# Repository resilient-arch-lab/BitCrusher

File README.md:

# BitCrusher: An Affordable, Open Source, Electromagnetic Fault Injection Platform
_NOTE: This repository is still under construction, and may be difficult to navigate in its current state_

Security researchers need attainable, effective tooling to secure computing infrastructure against physical attacks. Tools for hardware security research have been
getting cheaper and more effective over recent years, but EMFI tooling has been left behind. The cost of commercial EMFI tooling is typically on the order of tens to hundreds of thousands of dollars, and the highly-coupled proprietary equipment offers little insight to researchers developing or characterizing EMFI techniques. BitCrusher is being developed with the goal of addressing several challenges in this space:

- Supporting the continued improvement of open EMFI platform design techniques by contributing to the thread of research on the design of EMFI equipment
- Supporting the improvement of practical EMFI techniques and countermeasures through attainable and open domain specific instrumentation
- Lowering the high barrier to entry of replicating and expanding upon existing EMFI research by providing high performance equipment that is both affordable and easy to integrate with common existing hardware security instrumentation frameworks (e.g. ChipWhisperer)

## State of BitCrusher
BitCrusher was started as an undergraduate senior project in September 2025. Beginning April 2026, development efforts have been focused on working out design flaws and thoroughly verifying device performance.

See `/design.md` for status of ongoing design work.

## Licensing
Following the licensing guidelines of [OSHWA](https://oshwa.org/), the components of BitCrusher fall under a combination of OSI-approved licenses. The following licenses were selected with the goals of maximizing this work's benefit to the open hardware and open security research communities and ensuring potential commercial utilization of this work similarly benefits those communities.  

**Firmware and Software:** BitCrusher firmware and software fall under the [GNU Affero General Public License v3.0](https://www.gnu.org/licenses/agpl-3.0.html) (AGPL-3.0). This includes the BitCrusher device firmware (`/firmware`) and the host-side python interface (`/interface`).  

**Hardware design:** The design materials of BitCrusher (including but not limited to materials in `/design`, excluding those covered under the firmware / software licensing scheme) are licensed under the [CERN Open Hardware Licence Version 2 – Strongly Reciprocal](https://gitlab.com/ohwr/project/cernohl/-/wikis/uploads/819d71bea3458f71fba6cf4fb0f2de6b/cern_ohl_s_v2.txt) (CERN-OHL-S-2.0). 

**Documentation:** Current BitCrusher documentation, including but not limited to user guides / instructions, written documentation of the design, and written engineering work / documentation is under the [Creative Commons Attribution-ShareAlike 4.0 International](https://creativecommons.org/licenses/by-sa/4.0/) license (CC BY-SA 4.0). In cases where documentation is accompanied by code, such as simulations and calculations in `/design-resources`, the code falls under the AGPL-3.0 license while the written work falls under the CC BY-SA 4.0 license. 

While there is currently no sound structure for project governance, the policy for potential future contributions to the project's documentation is that the contributions should be CC BY-SA 4.0 licensed under the title "BitCrusher" and attributed to the respective contributor(s).  

**Branding:** Since this work was named after the [digital audio effect](https://en.wikipedia.org/wiki/Bitcrusher), as well as the fact that this project is a non-commercial endeavor, no restrictions apply to the use of the name BitCrusher.

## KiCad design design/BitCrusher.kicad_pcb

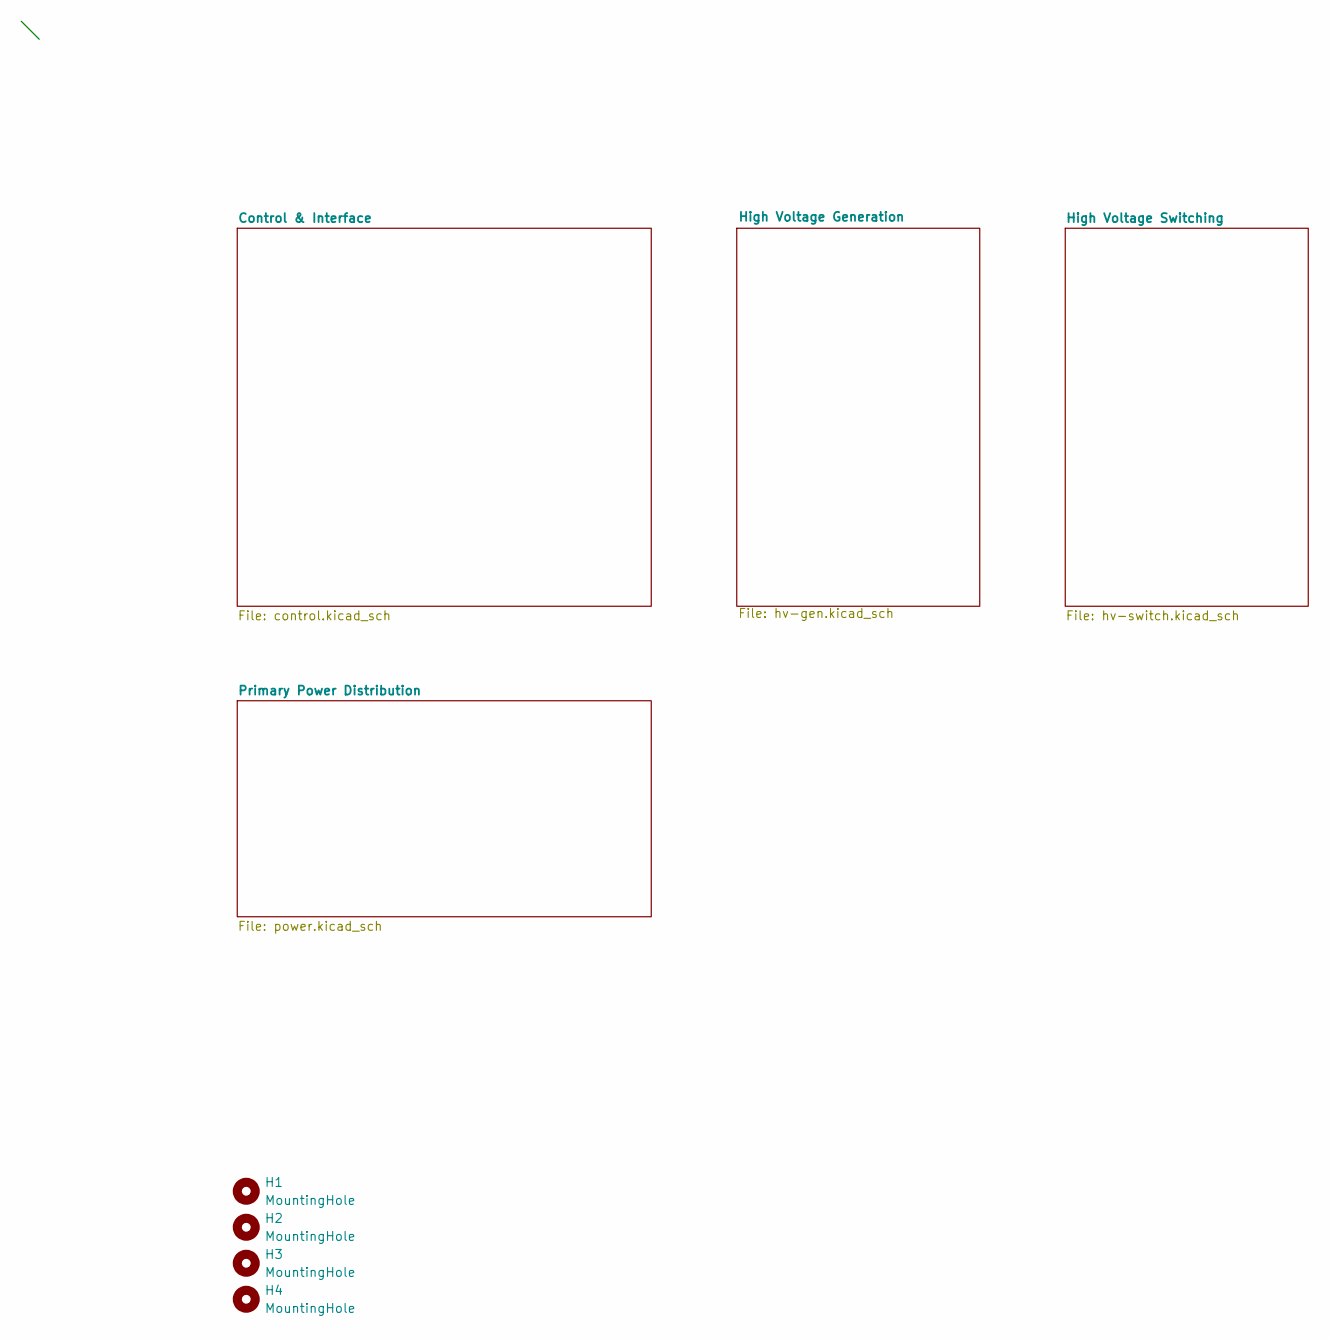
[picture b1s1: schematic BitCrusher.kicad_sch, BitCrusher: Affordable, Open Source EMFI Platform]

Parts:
H1, H2, H3, H4: MountingHole; MountingHole_3.2mm_M3

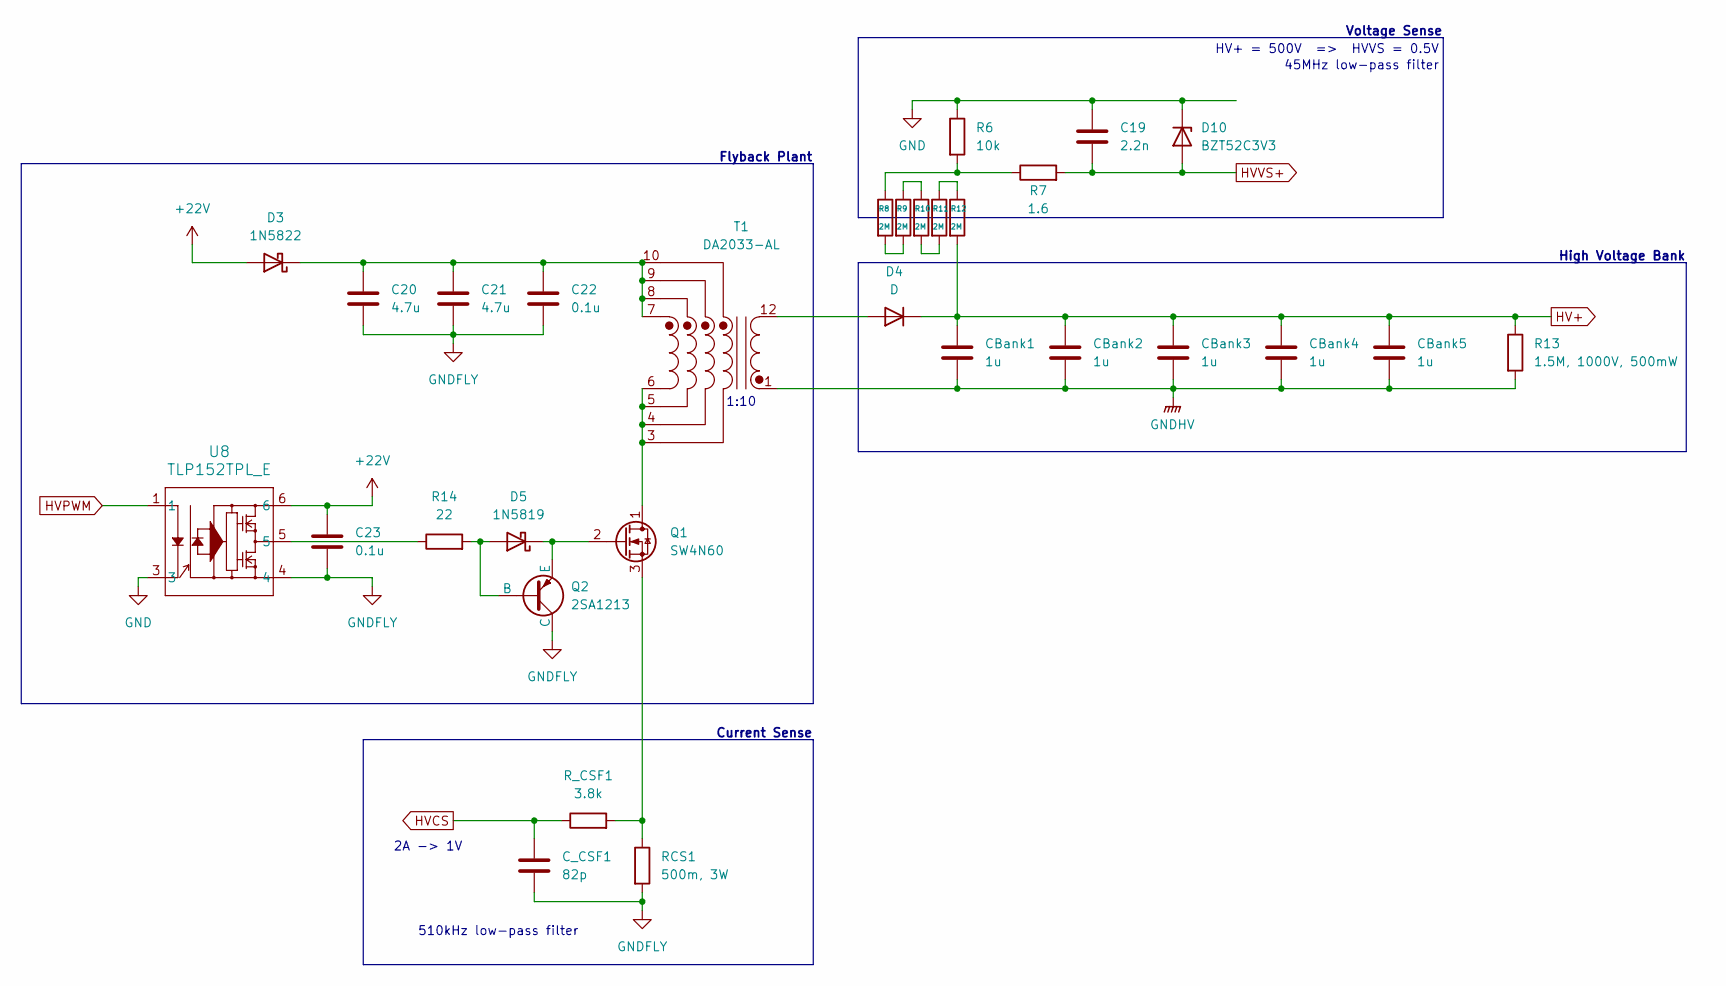
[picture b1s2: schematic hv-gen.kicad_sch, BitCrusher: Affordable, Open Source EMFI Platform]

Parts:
C19: 2.2n; C_0603_1608Metric
C20, C21: 4.7u; C_0402_1005Metric
C22: 0.1u; C_0402_1005Metric
C23: 0.1u; C_1206_3216Metric
CBank1, CBank2, CBank3, CBank4, CBank5: 1u; C_2220_5750Metric; JLCPCB# C784102
C_CSF1: 82p; C_0402_1005Metric
D3: 1N5822; D_DO-201AD_P12.70mm_Horizontal
D4: D; D_SMA
D5: 1N5819; D_SOD-323
D10: BZT52C3V3; D_SOD-123
Q1: SW4N60
Q2: 2SA1213; SOT-89-3
R6: 10k; R_0603_1608Metric
R7: 1.6; R_0603_1608Metric
R8, R9, R10, R11, R12: 2M; R_0805_2012Metric
R13: 1.5M, 1000V, 500mW; R_Axial_DIN0414_L11.9mm_D4.5mm_P15.24mm_Horizontal; JLCPCB# C30187384
R14: 22; R_0805_2012Metric
RCS1: 500m, 3W; R_2512_6332Metric
R_CSF1: 3.8k; R_0402_1005Metric
T1: DA2033-AL; SOP254P2413X978-12N
U8: TLP152TPL_E; TLP152_4P55X3P7_TOS

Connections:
+22V: C23.1, D3.2 (A), U8.6; also elsewhere on the board
GND: C19.1, D10.1 (K), R6.1, U8.3; also elsewhere on the board
GNDFLY: C20.2, C21.2, C22.2, C23.2, C_CSF1.2, Q2.C, RCS1.2, U8.4; also elsewhere on the board
HV+: CBank1.1, CBank2.1, CBank3.1, CBank4.1, CBank5.1, D4.1 (K), R12.2, R13.1; also elsewhere on the board
HVCS: C_CSF1.1, R_CSF1.1; also elsewhere on the board
HVPWM: U8.1; also elsewhere on the board
HVVS+: C19.2, D10.2 (A), R7.2; also elsewhere on the board
unnamed: C20.1, C21.1, C22.1, D3.1 (K), T1.7, T1.8, T1.9, T1.10
unnamed: D4.2 (A), T1.12
unnamed: D5.2 (A), Q2.B, R14.2
unnamed: D5.1 (K), Q1.2 (G), Q2.E
unnamed: Q1.1 (D), T1.3, T1.4, T1.5, T1.6
unnamed: Q1.3 (S), RCS1.1, R_CSF1.2
unnamed: R6.2, R7.1, R8.1
unnamed: R8.2, R9.2
unnamed: R9.1, R10.1
unnamed: R10.2, R11.2
unnamed: R11.1, R12.1
unnamed: R14.1, U8.5
PulseCS-: CBank1.2, CBank2.2, CBank3.2, CBank4.2, CBank5.2, R13.2, T1.1; also elsewhere on the board

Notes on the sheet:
High Voltage Bank
510kHz low-pass filter
Flyback Plant
2A -> 1V
1:10
Current Sense
HV+ = 500V => HVVS = 0.5V
Voltage Sense
45MHz low-pass filter

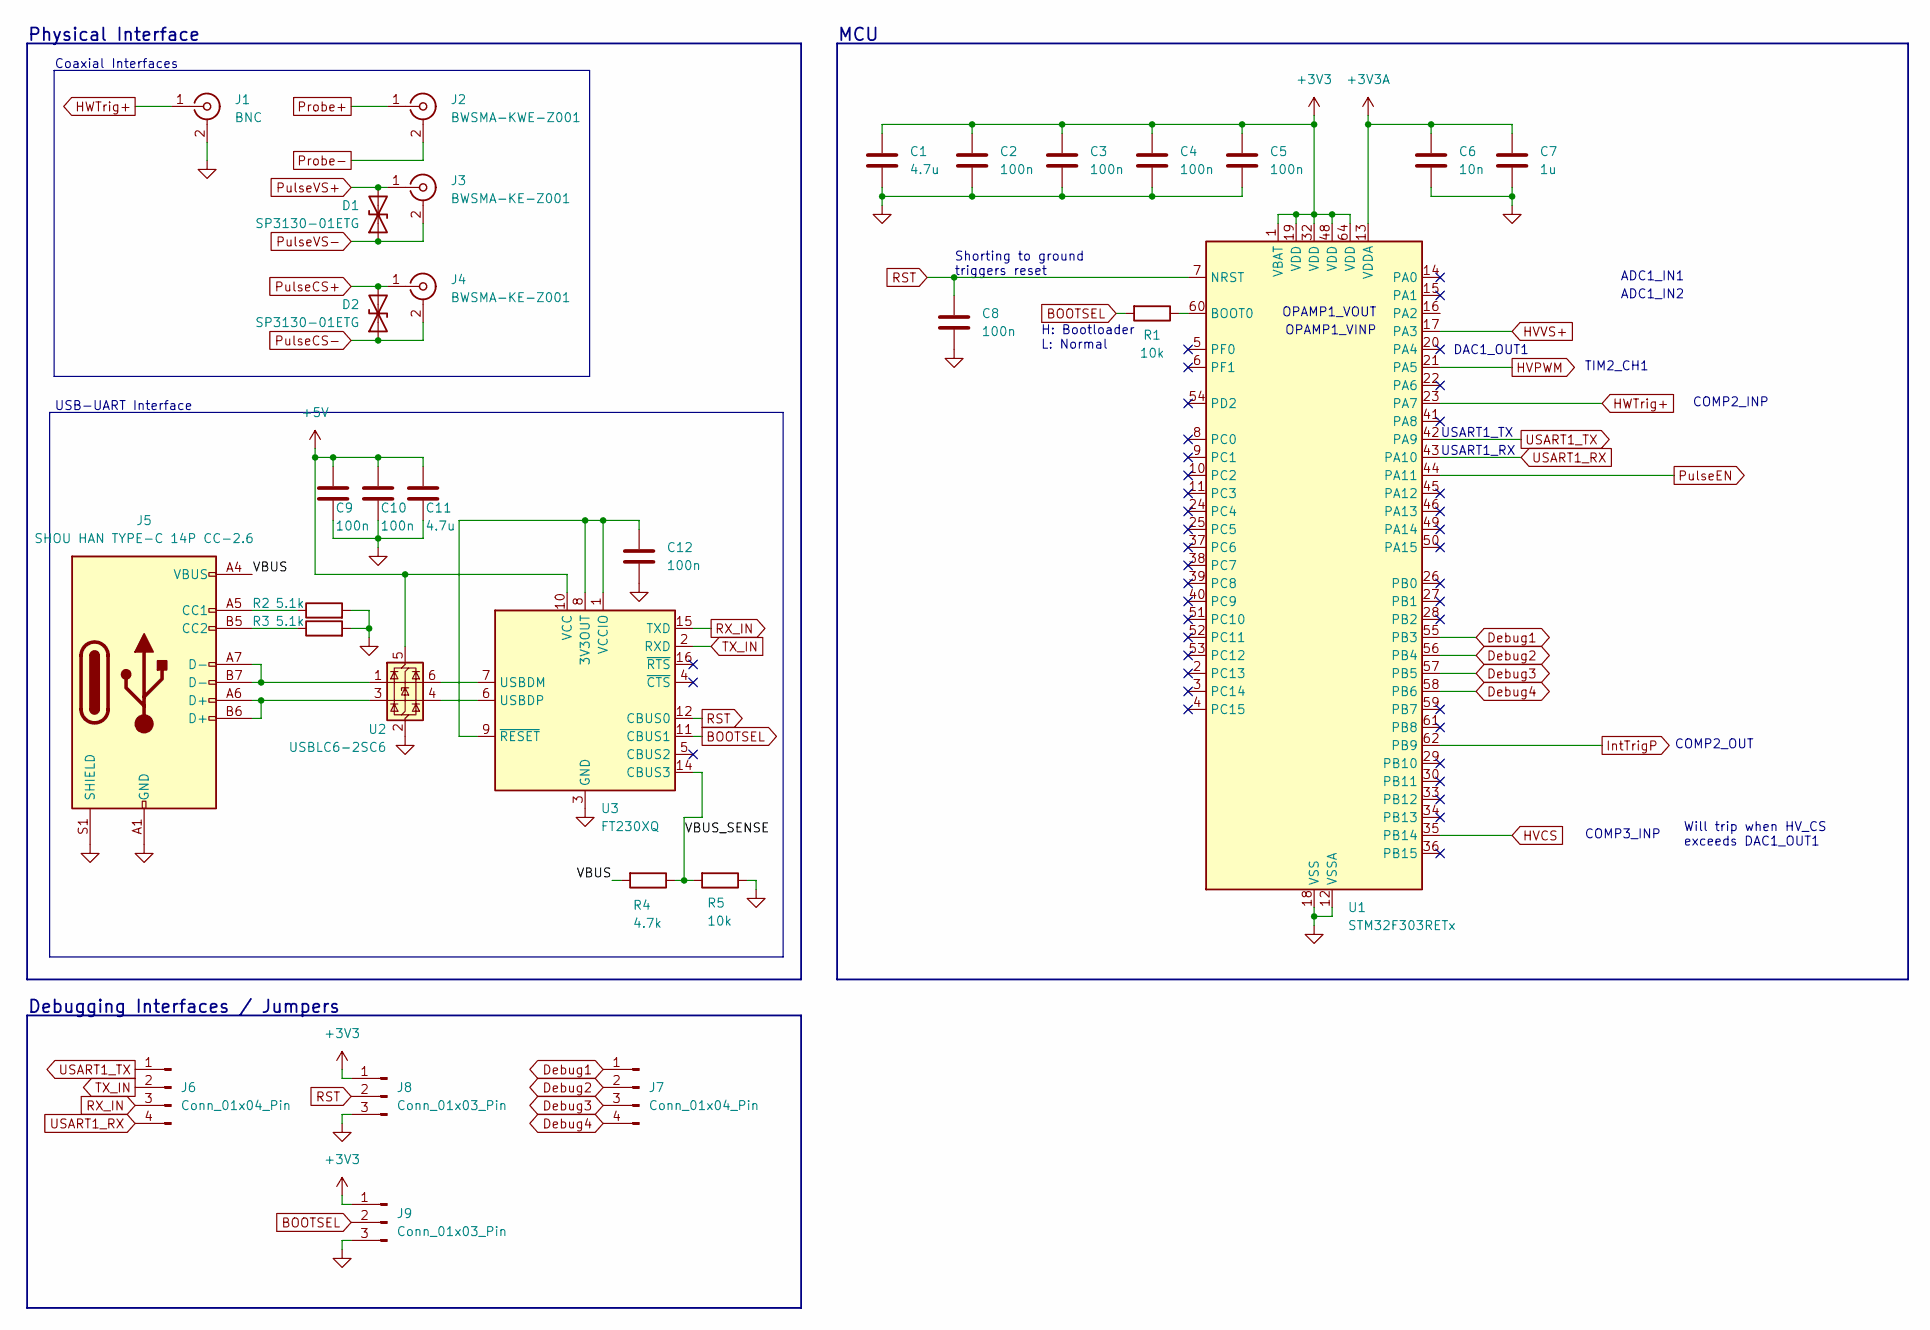
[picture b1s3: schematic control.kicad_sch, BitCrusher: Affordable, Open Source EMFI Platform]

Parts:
C1, C11: 4.7u; C_0402_1005Metric
C2, C3, C4, C5, C8, C9, C10, C12: 100n; C_0402_1005Metric
C6: 10n; C_0402_1005Metric
C7: 1u; C_0402_1005Metric
D1, D2: SP3130-01ETG; D_SOD-882
J1: BNC; KHBNC503511
J2: BWSMA-KWE-Z001; SMA_BAT_Wireless_BWSMA-KWE-Z001
J3, J4: BWSMA-KE-Z001; SMA_BAT_Wireless_BWSMA-KE-Z001
J5: SHOU HAN TYPE-C 14P CC-2.6; TYPE-C-TH_TYPE-C-14P-CC-2.6
J6, J7: Conn_01x04_Pin; PinHeader_1x04_P2.54mm_Vertical
J8, J9: Conn_01x03_Pin; PinHeader_1x03_P2.54mm_Vertical
R1, R5: 10k; R_0402_1005Metric
R2, R3: 5.1k; R_0603_1608Metric
R4: 4.7k; R_0402_1005Metric
U1: STM32F303RETx; LQFP-64_10x10mm_P0.5mm
U2: USBLC6-2SC6; SOT-23-6
U3: FT230XQ; QFN-16-1EP_4x4mm_P0.65mm_EP2.1x2.1mm

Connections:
+3V3: C1.1, C2.1, C3.1, C4.1, C5.1, C6.1, C7.1, J8.1, J9.1, U1.1 (VBAT), U1.13 (VDDA), U1.19 (VDD), U1.32 (VDD), U1.48 (VDD), U1.64 (VDD); also elsewhere on the board
+5V: C9.1, C10.1, C11.1, U2.5 (VBUS), U3.10 (VCC); also elsewhere on the board
/Control & Interface/VBUS: J5.A4 (VBUS), J5.A9 (VBUS), J5.B4 (VBUS), J5.B9 (VBUS), R4.2
/Control & Interface/VBUS_SENSE: R4.1, R5.2, U3.14 (CBUS3)
BOOTSEL: J9.2, R1.2, U3.11 (CBUS1)
Debug1: J7.1, U1.55 (PB3)
Debug2: J7.2, U1.56 (PB4)
Debug3: J7.3, U1.57 (PB5)
Debug4: J7.4, U1.58 (PB6)
GND: C1.2, C2.2, C3.2, C4.2, C5.2, C6.2, C7.2, C8.2, C9.2, C10.2, C11.2, C12.2, J1.2 (Ext), J5.A1 (GND), J5.A12 (GND), J5.B1 (GND), J5.B12 (GND), J5.S1 (SHIELD), J8.3, J9.3, R2.2, R3.2, R5.1, U1.12 (VSSA), U1.18 (VSS), U1.31 (VSS), U1.47 (VSS), U1.63 (VSS), U2.2 (GND), U3.3 (GND), U3.13 (GND), U3.17 (GND); also elsewhere on the board
HVCS: U1.35 (PB14); also elsewhere on the board
HVPWM: U1.21 (PA5); also elsewhere on the board
HVVS+: U1.17 (PA3); also elsewhere on the board
HWTrig+: J1.1 (In), U1.23 (PA7)
IntTrigP: U1.62 (PB9); also elsewhere on the board
unnamed: J5.A5 (CC1), R2.1
unnamed: J5.B5 (CC2), R3.1
unnamed: J5.A6 (D+), J5.B6 (D+), U2.3 (I/O2)
unnamed: J5.A7 (D-), J5.B7 (D-), U2.1 (I/O1)
unnamed: R1.1, U1.60 (BOOT0)
unnamed: C12.1, U3.1 (VCCIO), U3.8 (3V3OUT), U3.9 (~RESET)
unnamed: U2.6 (I/O1), U3.7 (USBDM)
unnamed: U2.4 (I/O2), U3.6 (USBDP)
Probe+: J2.1 (In); also elsewhere on the board
Probe-: J2.2 (Ext); also elsewhere on the board
PulseCS+: D2.2 (A2), J4.1 (In); also elsewhere on the board
PulseCS-: D1.1 (A1), D2.1 (A1), J3.2 (Ext), J4.2 (Ext); also elsewhere on the board
PulseEN: U1.44 (PA11); also elsewhere on the board
PulseVS+: D1.2 (A2), J3.1 (In); also elsewhere on the board
RST: C8.1, J8.2, U1.7 (NRST), U3.12 (CBUS0)
RX_IN: J6.3, U3.15 (TXD)
TX_IN: J6.2, U3.2 (RXD)
USART1_RX: J6.4, U1.43 (PA10)
USART1_TX: J6.1, U1.42 (PA9)

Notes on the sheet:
OPAMP1_VINP
ADC1_IN2
COMP2_INP
USART1_TX
H: Bootloader L: Normal
TIM2_CH1
ADC1_IN1
MCU
Debugging Interfaces / Jumpers
DAC1_OUT1
COMP2_OUT
Shorting to ground triggers reset
USB-UART Interface
USART1_RX
OPAMP1_VOUT
Coaxial Interfaces
Will trip when HV_CS exceeds DAC1_OUT1
COMP3_INP
Physical Interface

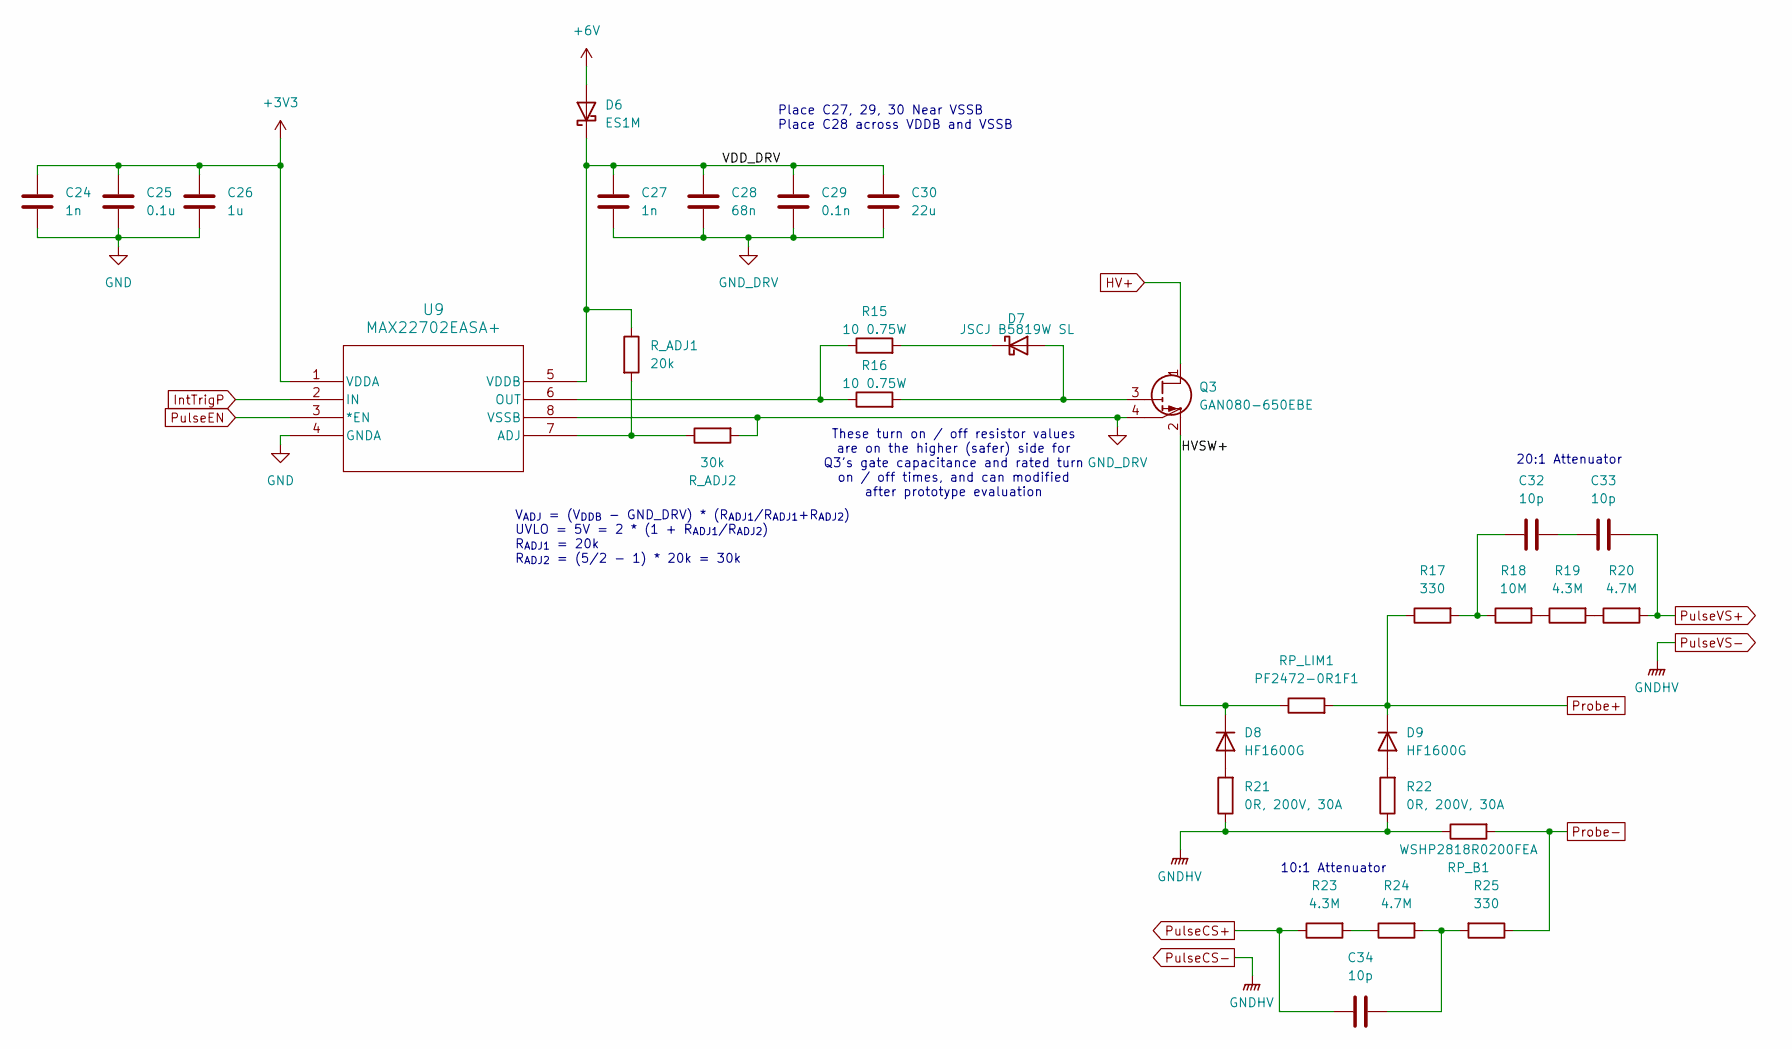
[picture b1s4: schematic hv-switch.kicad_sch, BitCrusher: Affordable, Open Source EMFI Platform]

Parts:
C24, C27: 1n; C_0402_1005Metric
C25: 0.1u; C_0402_1005Metric
C26: 1u; C_0402_1005Metric
C28: 68n; C_1206_3216Metric
C29: 0.1n; C_0402_1005Metric
C30: 22u; C_0603_1608Metric; JLCPCB# C60077
C32, C33, C34: 10p; C_0402_1005Metric
D6: ES1M; D_SMA
D7: JSCJ B5819W SL; D_SOD-123
D8, D9: HF1600G; D_DO-41_SOD81_P7.62mm_Horizontal
Q3: GAN080-650EBE; GAN080650EBEZ
R15, R16: 10 0.75W; R_1206_3216Metric
R17: 330; R_0603_1608Metric
R18: 10M; R_0603_1608Metric
R19, R23: 4.3M; R_0603_1608Metric
R20, R24: 4.7M; R_0603_1608Metric
R21, R22: 0R, 200V, 30A; R_2512_6332Metric
R25: 330; R_2512_6332Metric
RP_B1: WSHP2818R0200FEA
RP_LIM1: PF2472-0R1F1; TO-247-2_Horizontal_TabDown
R_ADJ1: 20k; R_0402_1005Metric
R_ADJ2: 30k; R_0402_1005Metric
U9: MAX22702EASA+; 21-0041-A_8L

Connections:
+3V3: C24.1, C25.1, C26.1, U9.1 (VDDA); also elsewhere on the board
+6V: D6.2 (A); also elsewhere on the board
/High Voltage Switching/HVSW+: D8.1 (K), Q3.2 (S), RP_LIM1.1
/High Voltage Switching/VDD_DRV: C27.1, C28.1, C29.1, C30.1, D6.1 (K), R_ADJ1.1, U9.5 (VDDB)
GND: C24.2, C25.2, C26.2, U9.4 (GNDA); also elsewhere on the board
GND_DRV: C27.2, C28.2, C29.2, C30.2, Q3.4 (SS), R_ADJ2.2, U9.8 (VSSB)
HV+: Q3.1 (D); also elsewhere on the board
IntTrigP: U9.2 (IN); also elsewhere on the board
unnamed: C32.1, C33.2
unnamed: C32.2, R17.2, R18.1
unnamed: C34.2, R24.2, R25.2
unnamed: D7.2 (A), Q3.3 (G), R16.2
unnamed: D7.1 (K), R15.2
unnamed: D8.2 (A), R21.2
unnamed: D9.2 (A), R22.2
unnamed: R18.2, R19.1
unnamed: R19.2, R20.1
unnamed: R23.2, R24.1
unnamed: R_ADJ1.2, R_ADJ2.1, U9.7 (ADJ)
unnamed: R15.1, R16.1, U9.6 (OUT)
Probe+: D9.1 (K), R17.1, RP_LIM1.2; also elsewhere on the board
Probe-: R25.1, RP_B1.2; also elsewhere on the board
PulseCS+: C34.1, R23.1; also elsewhere on the board
PulseCS-: R21.1, R22.1, RP_B1.1; also elsewhere on the board
PulseEN: U9.3 (*EN); also elsewhere on the board
PulseVS+: C33.1, R20.2; also elsewhere on the board

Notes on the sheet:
These turn on / off resistor values are on the higher (safer) side for Q3's gate capacitance and rated turn on / off times, and can modified after prototype evaluation
10:1 Attenuator
V_{ADJ} = (V_{DDB} - GND_DRV) * (R_{ADJ1}/R_{ADJ1}+R_{ADJ2}) UVLO = 5V = 2 * (1 + R_{ADJ1}/R_{ADJ2}) R_{ADJ1} = 20k R_{ADJ2} = (5/2 - 1) * 20k = 30k
20:1 Attenuator
Place C27, 29, 30 Near VSSB Place C28 across VDDB and VSSB

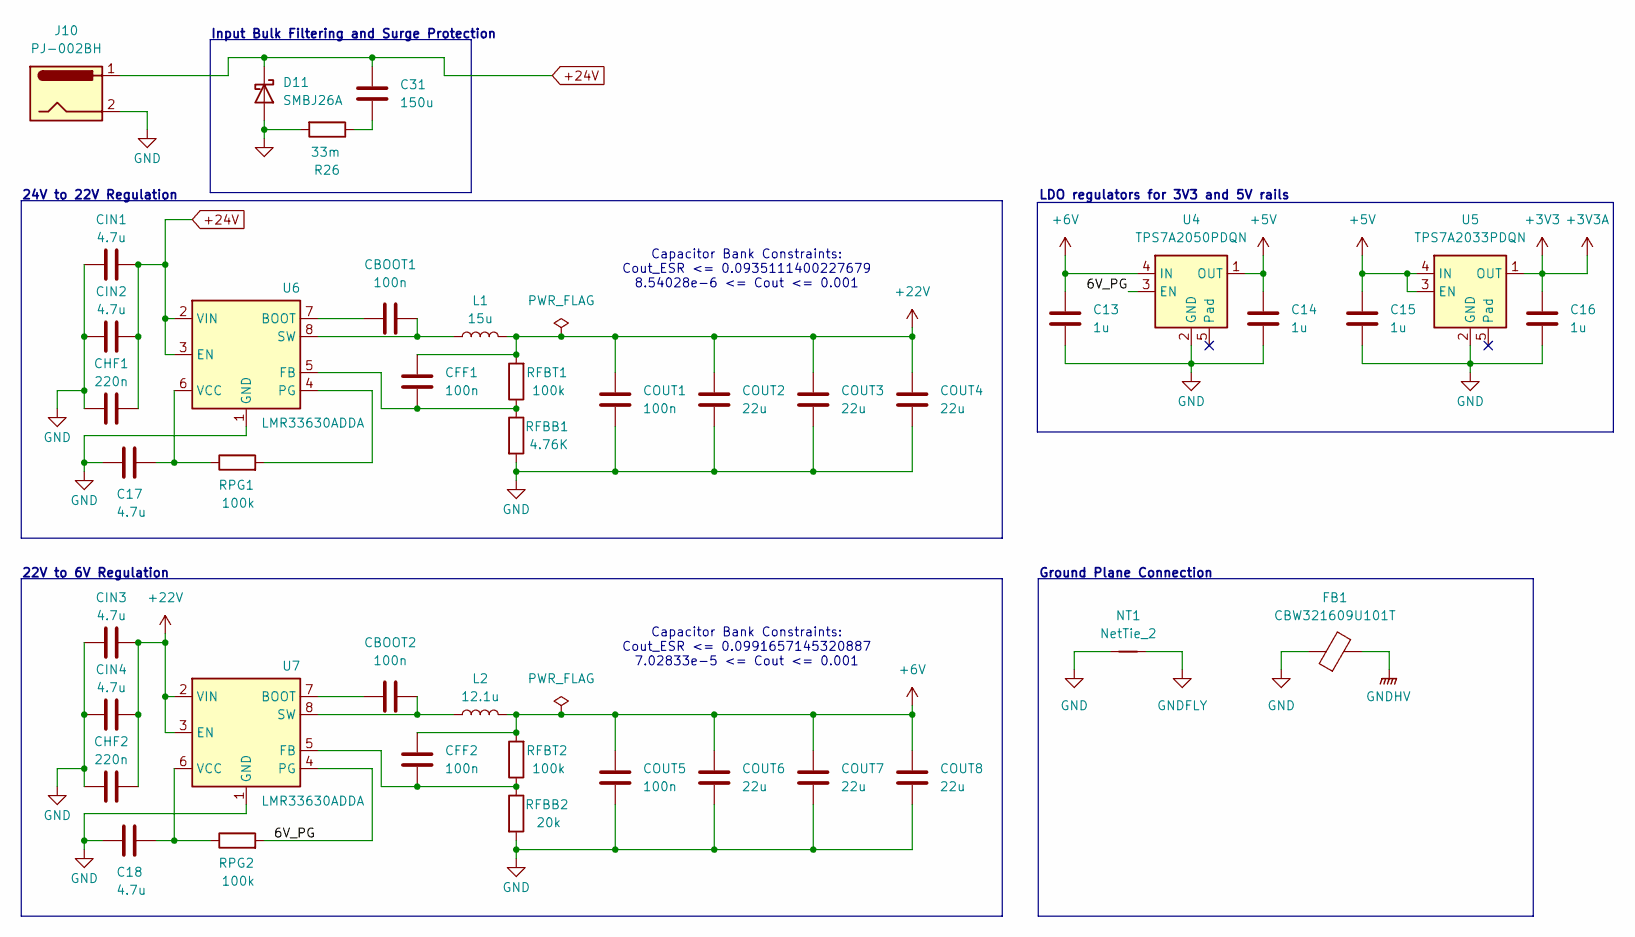
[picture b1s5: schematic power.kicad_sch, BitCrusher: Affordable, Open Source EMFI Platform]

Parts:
C13, C14, C15, C16: 1u; C_0402_1005Metric
C17, C18: 4.7u; C_1206_3216Metric
C31: 150u; C_Radial_D10.0mm_H20.0mm_P5.00mm
CBOOT1, CBOOT2: 100n; C_0402_1005Metric
CFF1, CFF2: 100n; C_0402_1005Metric
CHF1, CHF2: 220n; C_0805_2012Metric
CIN1, CIN2, CIN3, CIN4: 4.7u; C_1206_3216Metric
COUT1, COUT5: 100n; C_0402_1005Metric
COUT2, COUT3, COUT4, COUT6, COUT7, COUT8: 22u; C_1210_3225Metric
D11: SMBJ26A; D_SMB
FB1: CBW321609U101T; L_1206_3216Metric
J10: PJ-002BH; PJ-002B_CUI
L1: 15u; L_TechFuse_SL0630
L2: 12.1u; L_TechFuse_SL0630
NT1: NetTie_2; NetTie-2_SMD_Pad2.0mm
R26: 33m; R_0603_1608Metric
RFBB1: 4.76K; R_0603_1608Metric
RFBB2: 20k; R_0603_1608Metric
RFBT1, RFBT2: 100k; R_0603_1608Metric
RPG1, RPG2: 100k; R_0603_1608Metric
U4: TPS7A2050PDQN; Texas_X2SON-4_1x1mm_P0.65mm
U5: TPS7A2033PDQN; Texas_X2SON-4_1x1mm_P0.65mm
U6, U7: LMR33630ADDA; Texas_HSOP-8-1EP_3.9x4.9mm_P1.27mm_ThermalVias

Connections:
+3V3: C16.1, U5.1 (OUT); also elsewhere on the board
+5V: C14.1, C15.1, U4.1 (OUT), U5.3 (EN), U5.4 (IN); also elsewhere on the board
+6V: C13.1, CFF2.2, COUT5.2, COUT6.2, COUT7.2, COUT8.2, L2.2, RFBT2.2, U4.4 (IN); also elsewhere on the board
+22V: CFF1.2, CHF2.1, CIN3.1, CIN4.1, COUT1.2, COUT2.2, COUT3.2, COUT4.2, L1.2, RFBT1.2, U7.2 (VIN), U7.3 (EN); also elsewhere on the board
+24V: C31.1, CHF1.1, CIN1.1, CIN2.1, D11.1 (K), J10.1, U6.2 (VIN), U6.3 (EN)
/Primary Power Distribution/6V_PG: RPG2.2, U4.3 (EN), U7.4 (PG)
GND: C13.2, C14.2, C15.2, C16.2, C17.2, C18.2, CHF1.2, CHF2.2, CIN1.2, CIN2.2, CIN3.2, CIN4.2, COUT1.1, COUT2.1, COUT3.1, COUT4.1, COUT5.1, COUT6.1, COUT7.1, COUT8.1, D11.2 (A), FB1.1, J10.2, NT1.1, R26.2, RFBB1.2, RFBB2.2, U4.2 (GND), U5.2 (GND), U6.1 (GND), U6.9 (GND), U7.1 (GND), U7.9 (GND); also elsewhere on the board
GNDFLY: NT1.2; also elsewhere on the board
unnamed: C31.2, R26.1
unnamed: CBOOT1.1, U6.7 (BOOT)
unnamed: CFF1.1, RFBB1.1, RFBT1.1, U6.5 (FB)
unnamed: RPG1.2, U6.4 (PG)
unnamed: CBOOT1.2, L1.1, U6.8 (SW)
unnamed: C17.1, RPG1.1, U6.6 (VCC)
unnamed: CBOOT2.1, U7.7 (BOOT)
unnamed: CFF2.1, RFBB2.1, RFBT2.1, U7.5 (FB)
unnamed: CBOOT2.2, L2.1, U7.8 (SW)
unnamed: C18.1, RPG2.1, U7.6 (VCC)
PulseCS-: FB1.2; also elsewhere on the board

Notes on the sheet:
24V to 22V Regulation
Capacitor Bank Constraints: Cout_ESR <= 0.0991657145320887 7.02833e-5 <= Cout <= 0.001
LDO regulators for 3V3 and 5V rails
Capacitor Bank Constraints: Cout_ESR <= 0.0935111400227679 8.54028e-6 <= Cout <= 0.001
Ground Plane Connection
Input Bulk Filtering and Surge Protection
22V to 6V Regulation

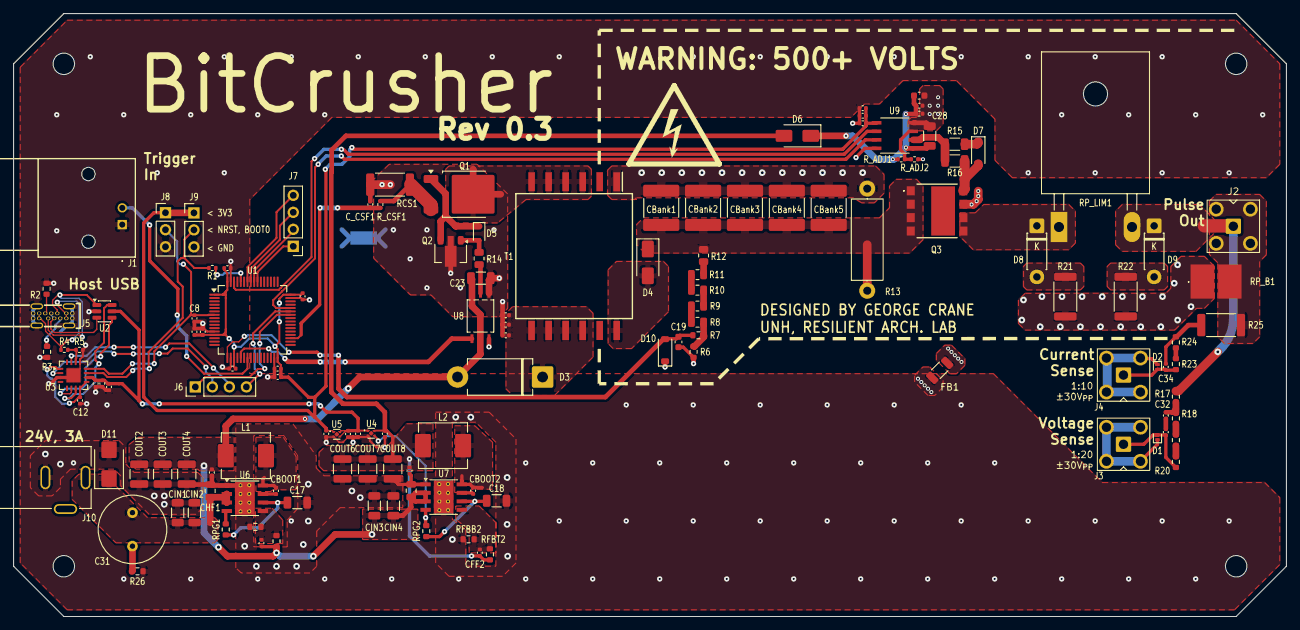
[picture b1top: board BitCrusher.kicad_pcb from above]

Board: 2 copper layers, 190.0 x 90.0 mm, 138 parts (1 on the bottom side), 77 nets.

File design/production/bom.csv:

Designator,Footprint,Quantity,Value,LCSC Part #
C_CSF1,402,1,82p,C107011
"C1, C11, C20, C21",402,4,4.7u,C2858031
"C10, C12, C2, C3, C4, C5, C8, C9, CBOOT1, CBOOT2, CFF1, CFF2, COUT1, COUT5",402,14,100n,C1525
"C13, C15, C26, C7",402,4,1u,C52923
"C14, C16",402,2,5u,C29266
"C17, C18, CIN1, CIN2, CIN3, CIN4",1206,6,4.7u,C29823
C19,603,1,2.2n,C1604
"C22, C25",402,2,0.1u,C1525
C23,1206,1,0.1u,C24497
"C24, C27",402,2,1n,C1523
C28,1206,1,68n,C711038
C29,402,1,0.1n,C343055
C30,603,1,22u,C60077
"C32, C33, C34",402,3,10p,C32949
C6,402,1,10n,C1524
"CBANK1, CBANK2, CBANK3, CBANK4, CBANK5",2220,5,1u,C784102
"CHF1, CHF2",805,2,220n,C5378
"COUT2, COUT3, COUT4, COUT6, COUT7, COUT8",1210,6,22u,C21397
"D1, D2",D_SOD-882,2,SP3031-01ETG,C207283
D10,D_SOD-123,1,BZT52C3V3,C19077396
"D3, D6",D_DO-201AD_P12.70mm_Horizontal,2,1N5822,C2476
D4,D_SMA,1,D,C64958
D5,D_SOD-323,1,1N5819,C191023
D7,D_SOD-123,1,D_Schottky,C8598
"D8, D9",D_DO-41_SOD81_P7.62mm_Horizontal,2,HF1600G,C411154
FB1,1206,1,CBW321609U101T,C91466
J1,KHBNC503511,1,BNC,C2837587
J10,PJ-002B_CUI,1,PJ-002BH,C22359705
J2,SMA_BAT_Wireless_BWSMA-KWE-Z001,1,BWSMA-KWE-Z001,C496551
"J3, J4",SMA_BAT_Wireless_BWSMA-KE-Z001,2,BWSMA-KE-Z001,C496549
J5,TYPE-C-TH_TYPE-C-14P-CC-2.6,1,SHOU HAN TYPE-C 14P CC-2.6,C5187475
"J6, J7",PinHeader_1x04_P2.54mm_Vertical,2,Conn_01x04_Pin,
"J8, J9",PinHeader_1x03_P2.54mm_Vertical,2,Conn_01x03_Pin,
L1,L_TechFuse_SL0630,1,15u,C22463824
L2,L_TechFuse_SL0630,1,12.1u,C22463823
Q1,SW4N60,1,SW4N60,C381523
Q2,SOT-89-3,1,2SA1213,C20069144
Q3,GAN080650EBEZ,1,GAN080-650EBE,C20235155
R_ADJ1,402,1,20k,C25545
R_ADJ2,402,1,30k,C49652989
R_CSF1,402,1,3.8k,C51721
"R1, R5",402,2,10k,C25744
"R10, R11, R12, R8, R9",805,5,2M,C26112
R13,R_Axial_DIN0414_L11.9mm_D4.5mm_P15.24mm_Horizontal,1,"1.5M, 1000V, 500mW",C30187384
R14,805,1,22,C17561
"R15, R16",1206,2,10 0.75W,C873970
R17,603,1,330,C23138
R18,603,1,10M,C7250
"R19, R23",603,2,4.3M,C2930152
"R2, R3",603,2,5.1k,C23186
"R20, R24",603,2,4.7M,C23163
"R21, R22",2512,2,"0R, 200V, 30A",C2907567
R25,2512,1,330,C4134246
R26,603,1,0,C21189
R4,402,1,4.7k,C25900
R6,603,1,60k,C6460576
R7,603,1,1.6,C2930144
RCS1,2512,1,"500m, 3W",C2904268
RFBB1,603,1,4.76K,C23045
RFBB2,603,1,20k,C4184
"RFBT1, RFBT2, RPG1, RPG2",603,4,100k,C25803
RP_B1,WSHP2818R0200FEA,1,WSHP2818R0200FEA,C2090752
RP_LIM1,TO-247-2_Horizontal_TabDown,1,PF2472-0R1F1,C3387781
T1,SOP254P2413X978-12N,1,DA2033-AL,C5142798
U1,LQFP-64_10x10mm_P0.5mm,1,STM32F303RETx,C183214
U2,SOT-23-6,1,USBLC6-2SC6,C2827654
U3,QFN-16-1EP_4x4mm_P0.65mm_EP2.1x2.1mm,1,FT230XQ,C128629
U4,Texas_X2SON-4_1x1mm_P0.65mm,1,TPS7A2050PDQN,C2866499
U5,Texas_X2SON-4_1x1mm_P0.65mm,1,TPS7A2033PDQN,C2871641
"U6, U7",Texas_HSOP-8-1EP_3.9x4.9mm_P1.27mm_ThermalVias,2,LMR33630ADDA,C2866787
U8,TLP152_4P55X3P7_TOS,1,TLP152TPL_E,C150122
U9,21-0041-A_8L,1,MAX22702EASA+,C17268134

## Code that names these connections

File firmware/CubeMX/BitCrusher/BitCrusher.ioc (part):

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Mcu.Name=STM32F303R(D-E)Tx
Mcu.Package=LQFP64
Mcu.UserName=STM32F303RETx
PA0.GPIOParameters=GPIO_Label
PA0.GPIO_Label=HVSense+
PA0.Mode=IN1-Differential
PA0.Signal=ADC1_IN1
PA1.GPIOParameters=GPIO_Label
PA1.GPIO_Label=HVSense-
PA1.Mode=IN1-Differential
PA1.Signal=ADC1_IN2
PA10.Mode=Asynchronous
PA10.Signal=USART1_RX
PA11.GPIOParameters=GPIO_Label
PA11.GPIO_Label=PulseEN
PA11.Signal=GPIO_Output
PA2.Mode=PGA Not Connected
PA2.Signal=OPAMP1_VOUT
PA3.Mode=PGA Not Connected
PA3.Signal=OPAMP1_VINP
PA4.Signal=COMP_DAC11_group
PA5.GPIOParameters=GPIO_Label
PA5.GPIO_Label=HVPWM
PA5.Signal=S_TIM2_CH1_ETR
PA6.Signal=S_TIM3_CH1
PA7.GPIOParameters=GPIO_Label
PA7.GPIO_Label=HWTrig+
PA7.Mode=INP
PA7.Signal=COMP2_INP
PA9.Mode=Asynchronous
PA9.Signal=USART1_TX
PB14.GPIOParameters=GPIO_Label
PB14.GPIO_Label=HVCS
PB14.Mode=INP
PB14.Signal=COMP3_INP
PB9.GPIOParameters=GPIO_Label
PB9.GPIO_Label=IntTrig+
PB9.Mode=ExternalOutput
PB9.Signal=COMP2_OUT
PD2.Signal=S_TIM3_ETR
RCC.HSE_VALUE=8000000
RCC.SYSCLKFreq_VALUE=72000000
RCC.SYSCLKSourceVirtual=RCC_SYSCLKSOURCE_PLLCLK
board=custom

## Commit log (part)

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2025-11-08 added kicad project
2025-11-08 added .gitignore
2025-11-09 started microcontroller setup
2025-11-09 added cubemx project for microcontroller
2025-11-10 started primary power distribution design
2025-11-12 hv generation planning
2025-11-26 added CubeMX files, worked on microcontroller schematic
2025-11-28 figuring out triggering scheme
2025-12-01 started USB-C interface design
2025-12-05 Working on GaNFET driver circuit for HV switching
2025-12-07 Working on high voltage switching
2025-12-20 assembling final components for HV switching
2025-12-21 Continuing work on HV switching and primary power distribution
2025-12-26 Finished flyback voltage sense divider
2025-12-27 Working on probe voltage and current sense circuits
2025-12-28 outlining python interface
2025-12-30 Trying to figure out high side driver level shifting
2025-12-31 Fixed gate drive UVLO
2026-01-04 Added low pass filter to high voltage sensing circuit
2026-01-08 Switched to FT230X UART bridge
2026-01-12 Finished new UART bridge circuit
2026-01-12 moved cubemx project files
2026-01-12 organizing
2026-01-12 expanding interface plan
2026-01-12 finished project initialization
2026-01-12 restructuring
2026-01-12 starting PI control for flyback converter
2026-01-13 buck regulator power calculations
2026-01-13 Primary power buck regulator
2026-01-13 Almost finished primary power regulation
2026-01-14 working on measurement buffers
2026-01-17 Working on measure buffers and assigning footprints
2026-01-18 generate C protocol header defs from python defs
2026-01-19 figuring out FT230X GPIO
2026-01-19 basic protocol testing
2026-01-21 models actually compile in mtk11 now yay
2026-01-21 not quite working...
2026-01-21 working on resistor network equivalence calculations
2026-01-23 working network finding logic!
2026-01-25 finished, got results I needed
2026-01-25 Added resistor networks
2026-01-26 more footprint assignment
2026-01-26 Footprint assignment / part selection
2026-01-26 More footprint assignment and component selection
2026-01-28 More footprint assignment (almost done)
2026-01-28 Done with component selection / footprint assignment
2026-01-28 Cleanup
2026-01-28 finalization
2026-01-29 trace current calculations
2026-01-29 Starting PCB layout
2026-01-29 Layout Work
2026-01-30 Primary power layout
2026-02-02 More layout work
2026-02-04 Working on layout
2026-02-06 Swapped resistor networks for shunt resistors
2026-02-08 Fixing DRC stuff
2026-02-09 Fixed (almost) all DRC errors
2026-02-09 Almost done with layout
2026-02-11 Fixing layout and parts selection issues for prototype run
2026-02-11 added working BOM
2026-02-11 More little fixes
2026-02-11 Switched to larger via's for big cost saving
2026-02-12 Added moe
2026-02-12 finalizing prototype
2026-02-12 Production
2026-02-15 firmware / interface work
2026-02-22 starting 3D modeling of case
2026-02-22 Added missing 3d models
2026-02-23 tests with dev board
2026-02-23 protocol testing with dev board
2026-02-24 getting and setting arming parameters
2026-02-24 fixed message handling bugs
2026-02-24 using unittest framework for testing
2026-02-25 arming handshake protocol
2026-02-25 testing arming handshake protocol
2026-02-26 working on flyback control system
2026-02-27 control system
2026-02-27 ftd2xx setup
2026-02-28 working ft230x GPIO configuration
2026-02-28 bootloader work
2026-03-01 Starting rev 0.2
2026-03-01 Increased trace width from flyback shunt resistor to ground
2026-03-02 fixed component value typo
2026-03-02 added open bootloader submodule
2026-03-02 openbootloader integration
2026-03-03 trying and failing to figure out open bootloader
2026-03-03 expanded protocol to include bootloader command
2026-03-04 working uart bootloader with testing device
2026-03-04 switched to correct bootloader UART pins
2026-03-04 fixing armed loop
2026-03-04 testing flyback control
2026-03-06 Fixed PNP turnoff circuit, increased measurement buffer spacing
2026-03-07 flyback sim
2026-03-07 moved in old flyback converter simulation
2026-03-08 moved in old flyback sim
2026-03-08 more flyback sim work
2026-03-09 corrected Q1 footprint and orientation
2026-03-10 flyback voltage sense filter testing
2026-03-10 Reduced HVVS filter capacitance
2026-03-11 no sim errors now
2026-03-11 mostly working control system
2026-03-11 extended ADC sampling time
2026-03-12 MCU feedback support
2026-03-12 debugging control system
2026-03-13 Adjusted UVLO resistors
2026-03-14 Figuring out HV switching issue
2026-03-15 tweaked high voltage fet driver circuit and layout
2026-03-15 Modified high voltage gate drive circuit and layout, added net tie from GND to flyback converter GND
2026-03-17 fixed PulseEN polarity
2026-03-18 Altered HVCS filter, replaced some high current traces with filled zones, added labels
2026-03-24 removed open bootloader artifacts
2026-03-24 configuring FPGA TDC calibration
2026-03-24 added ferrite bead between HVGND and GND
2026-03-25 working on tdc testing
2026-03-25 success
2026-03-25 Improved decoupling
2026-03-26 export raw test data
2026-03-26 got more results
2026-03-27 Rev 0.2 Production
2026-03-28 PID tuning
2026-04-06 working UART on rev2 prototype
2026-04-07 removed openbl submodule (again ?)
2026-04-07 cleaned up Device
2026-04-07 updated deps
2026-04-07 typing fixes
2026-04-07 control system tuning
2026-04-08 Fixed BNC footprint polarity
2026-04-08 husky trigger forwarding
2026-04-09 fixed internal trigger pin setting
2026-04-09 comparator disable bypass
2026-04-09 ender3v3 control
2026-04-13 working on figures
2026-04-14 setting up demonstration
2026-04-14 async arming
2026-04-14 bugfix
2026-04-14 changed bitcrusher benchmark
2026-04-15 reworking BitCrusher FPGA TDC experiment
2026-04-15 async arming bug fix
2026-04-16 updated plots
2026-04-18 preparing URC presentation
2026-04-18 working on demonstration
2026-04-19 working on demonstration code
2026-04-19 added option to not print feedback from flyback control system when armed
2026-04-19 improving demonstration code
2026-04-20 URC demonstration notebook
2026-04-20 final fault positions
2026-04-20 final demo positions
2026-04-23 moved high voltage switching component selection from old repo
2026-04-25 repo cleanup
2026-04-25 flyback control sys
2026-04-25 enable flashing of release builds
2026-04-26 disabled ADC1 WDG IT
2026-04-26 design files cleanup
2026-06-22 control system reworking
2026-06-29 working on acausal model
